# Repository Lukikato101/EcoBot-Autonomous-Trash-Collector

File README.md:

# EcoBot Autonomous Trash Collector

EcoBot is a prototype for an autonomous trash collection robot designed to streamline waste pickup in public spaces and improve environmental cleanliness. This project showcases a multidisciplinary approach combining mechanical design, embedded systems, and intelligent sensing.

## Project Summary

EcoBot integrates:
- autonomous navigation logic for route planning and obstacle avoidance
- AI-based object detection for identifying trash items
- embedded control for motors, sensors, and actuators
- mechanical design for effective trash intake and chassis stability

The repository includes CAD models, electronics design artifacts, and supporting documentation for the robot platform.

## Key Features

- Autonomous path planning and movement control
- Trash detection using computer vision methods
- Hardware-ready embedded system design
- Modular mechanical structure for rapid prototyping
- Focus on real-world usability and environmental impact

## Technical Stack
- Mechanical design: FreeCAD
- Embedded systems: Arduino-compatible microcontroller concepts
- AI / vision: YOLO-style object detection concepts
- Robotics middleware: ROS2 planned for future scalability
- Documentation & design review: KiCad, CAD files, and project notes

## Repository Structure

- `Embeddeds/` – electronics and firmware-related files
- `Mechanicals/` – CAD mechanical design files for the robot chassis
- `assets/references/` – supporting diagrams, reference materials, and design inspiration

## Why This Project Matters

EcoBot demonstrates the ability to deliver cross-functional engineering projects that blend hardware and software. It highlights practical skills in robotics design, embedded development, and intelligent sensing systems — all highly valuable for engineering and automation roles.

## Career Relevance

This project is ideal to mention in job applications because it reflects:
- hands-on prototyping experience
- multidisciplinary collaboration potential
- a clear focus on solving a social and environmental problem
- readiness to work with modern robotics and AI technologies

## Next Steps

Future enhancements planned for EcoBot include:
- full ROS2 integration for advanced autonomous behavior
- improved object detection accuracy with training datasets
- a remote monitoring dashboard for status visualization
- real-world field testing and performance validation

---

If you want, I can also help create a concise project summary for your resume or LinkedIn profile.

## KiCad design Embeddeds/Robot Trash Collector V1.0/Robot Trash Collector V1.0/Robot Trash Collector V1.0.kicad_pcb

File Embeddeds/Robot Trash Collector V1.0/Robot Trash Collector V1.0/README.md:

# Robot Trash Collector V1.0

## Project Overview
This project is a PCB-based embedded control system for a small autonomous robot designed for waste collection. The board integrates the main controller, motor-driving circuitry, power regulation, and sensing support in a compact and modular design.

The purpose of this system is to provide a reliable electronic platform for autonomous movement, basic sensing, and control of the robot's actuators. It is intended for educational use, prototyping, and further engineering development.

## Project Purpose
The purpose of this project is to provide a reliable electronic platform for controlling a mobile robot. The design aims to support:
- Precise motor control for movement
- Wireless communication capabilities through the main controller
- Sensor-based operation for improved automation
- A compact PCB layout suitable for prototyping and further development

## Main Hardware Components
The current design includes the following key components:
- ESP32-C3-WROOM-02: Main microcontroller module with Wi-Fi and Bluetooth LE support
- TB6612FNG: Dual H-bridge motor driver used to control DC motors efficiently
- AP2112K-3.3: 3.3V low-dropout voltage regulator for stable logic power
- MPU-6050: Motion and orientation sensor for attitude and motion feedback
- Push buttons: Reset and user interaction input
- Power and motor connectors: External supply and actuator connection points

## Functional Description
The board is organized around a simple control architecture:
1. Power is supplied through the main input connector.
2. The regulator converts the supply voltage into a stable 3.3V rail for the controller and sensing circuitry.
3. The ESP32-C3 module acts as the central controller for processing signals and managing communication.
4. The TB6612FNG motor driver receives control signals and drives the robot's motors.
5. The MPU-6050 provides motion-related feedback that can be used for navigation or stabilization logic.

This structure makes the design easy to understand, modify, and expand for future improvements.

## Project Structure
The workspace contains the following important files:
- Robot Trash Collector V1.0.kicad_sch: Schematic design
- Robot Trash Collector V1.0.kicad_pcb: PCB layout
- Robot Trash Collector V1.0.kicad_pro: KiCad project configuration
- Robot Trash Collector V1.0.step: 3D model export of the PCB
- Projects Image/: Reference images and project visuals
- docs/Block_Diagram.svg: System-level block diagram
- docs/production-checklist.md: Production readiness checklist
- docs/BOM.csv: Starter bill of materials

## How to Use This Project
1. Install KiCad on your computer.
2. Open the project file named Robot Trash Collector V1.0.kicad_pro.
3. Review the schematic and PCB layout carefully.
4. Run design rule checks (DRC) and electrical rule checks (ERC) before fabrication.
5. Verify component footprints and connector pin assignments before manufacturing.

## Production Readiness Notes
This design is close to a prototype-ready state, but it should still be reviewed carefully before mass production or a final manufacturing run. The most important items to confirm are:
- Proper component footprints and pin mapping
- Correct power polarity and regulator selection
- Adequate decoupling and grounding
- Clear silkscreen labeling for connectors and test points
- A verified prototype build and functional test

## Visual Documentation
The following visual assets are available to help understand the project more clearly:

- Schematic and PCB layout: Open the KiCad project files in the project folder
- Block diagram: [docs/Block_Diagram.svg](docs/Block_Diagram.svg)
- Project image preview: [Projects Image/Robot Trash Collector V1.0.svg](Projects%20Image/Robot%20Trash%20Collector%20V1.0.svg)
- Additional screenshots: [Projects Image](Projects%20Image)

These visuals provide a quick overview of the overall architecture, component placement, and system layout.

## Development Notes
This design is intended for educational, prototyping, and engineering development purposes. It can be further improved by adding:
- A complete bill of materials (BOM)
- Firmware documentation
- Testing procedures and calibration instructions
- A finalized assembly drawing
- A more detailed schematic annotation for easier manufacturing review

## Notes for Production Readiness
Before sending the board to fabrication, it is strongly recommended to:
- Review the schematic and PCB layout carefully in KiCad
- Verify all footprints and pin assignments
- Confirm power polarity and regulator compatibility
- Check grounding, decoupling, and connector labeling
- Build and test a prototype before final production

## Summary
Robot Trash Collector V1.0 is a compact embedded electronics project that combines microcontroller control, motor driving, sensor integration, and power management in a single PCB design. It provides a solid foundation for building and expanding an autonomous robotic system.

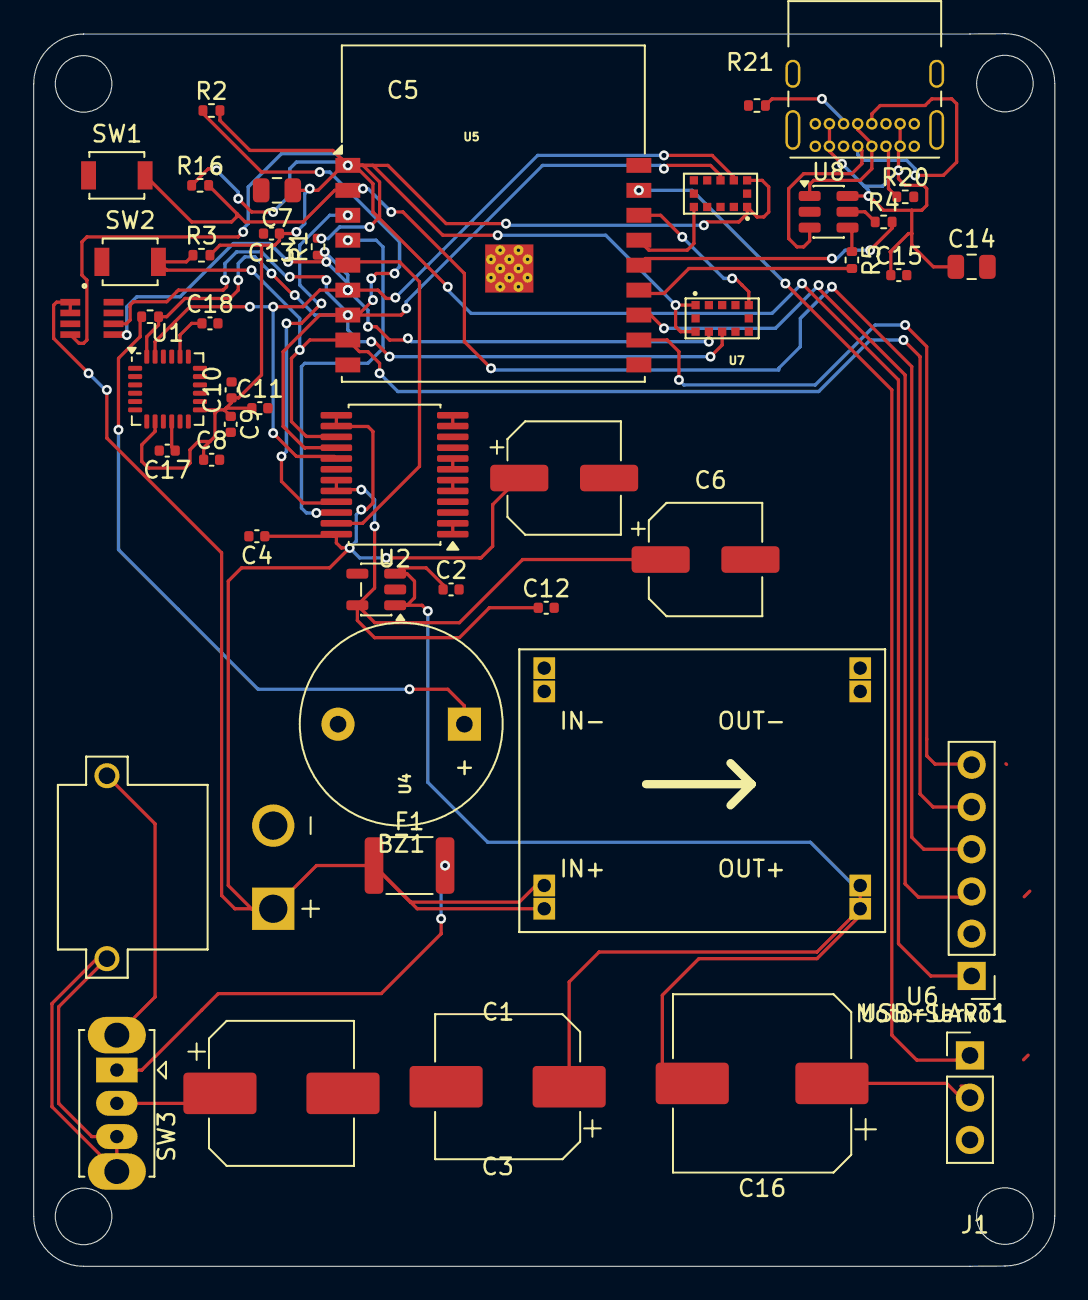
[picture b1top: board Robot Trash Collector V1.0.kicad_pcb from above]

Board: 2 copper layers, 61.4 x 74.1 mm, 45 parts (0 on the bottom side), 35 nets.

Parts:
BZ1: Buzzer; Buzzer_12x9.5RM7.6
C1, C3: 220uF; CP_Elec_8x10.5
C2, C4, C8, C9, C10, C11, C12, C13, C15, C17: 100nF; C_0402_1005Metric
C5, C6: 100uF; CP_Elec_6.3x7.7
C7, C14: 10uF; C_0805_2012Metric
C16: 470uF; CP_Elec_10x10.5
C18: 2.2nF; C_0402_1005Metric
F1: Polyfuse_Small; Fuse_1812_4532Metric
J1: USB_C_Receptacle_USB2.0_16P; USB_C_Receptacle_GCT_USB4085
J2: XT30PW-M; AMASS_XT30PW-M
MotorServo1: Conn_01x03; PinHeader_1x03_P2.54mm_Vertical
R1, R2: 4.7K; R_0402_1005Metric
R3, R16: 10K; R_0402_1005Metric
R4, R5: 22; R_0402_1005Metric
R19: 220; R_0402_1005Metric
R20, R21: 5.1K; R_0402_1005Metric
SW1: SW_Push_Button_Reset; SW_SPST_B3U-1000P
SW2: SW_Push_Button_Boot; SW_SPST_B3U-1000P
SW3: SW_SPST; SW_Slide_SPDT_Straight_CK_OS102011MS2Q
U1: MPU-6050; InvenSense_QFN-24_4x4mm_P0.5mm
U2: TB6612FNG; SSOP-24_5.3x8.2mm_P0.65mm
U3: MP1584 Module; DC-BRICK
U4: INA219; SOT23-8
U5, U7: VL53L0X; SENSOR_VL53L0X
U6: ESP32-C3-WROOM-02
U8: USBLC6-2SC6; SOT-23-6
U9: AP2112K-3.3; SOT-23-5
USB-UART1: Conn_01x06; PinHeader_1x06_P2.54mm_Vertical

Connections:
3V3: C7.1, C8.1, C9.1, C10.1, C11.1, C13.1, R1.2, R2.2, R3.2, R16.1, U1.8 (VLOGIC), U1.13 (VDD), U4.4 (VCC), U5.1 (AVDDVCSEL), U5.11 (AVDD), U6.1 (3V3), U7.1 (AVDDVCSEL), U7.11 (AVDD), USB-UART1.1
+3.3V AP: C6.1, C12.1, U2.19 (STBY), U2.20 (VCC), U9.5 (VOUT)
+5V MP: C2.1, C3.1, C16.2, U3.OUT1+ (VOUT+), U3.OUT2+ (VOUT+), U9.1 (VIN), U9.3 (EN)
+5V_USB: C14.1, C15.1, J1.A4 (VBUS), J1.A9 (VBUS), J1.B4 (VBUS), J1.B9 (VBUS), U8.6 (I/O1)
BAT 7.4V: C1.1, C4.1, C5.1, F1.1, J2.P, SW3.2 (B), U2.13 (VM2), U2.14 (VM3), U2.24 (VM1), U3.IN1+ (VIN+), U3.IN2+ (VIN+), U4.1 (VIN+), U4.2 (VIN-)
BOOT: R3.1, SW2.2, U2.15 (PWMB), U6.8 (IO9), USB-UART1.5
GND: BZ1.2 (-), C1.2, C2.2, C3.2, C4.2, C5.2, C6.2, C7.2, C8.2, C9.2, C10.2, C11.2, C12.2, C13.2, C14.2, C15.2, C17.2, C18.2, J1.A1 (GND), J1.A12 (GND), J1.B1 (GND), J1.B12 (GND), J1.S1 (SHIELD), J2.N, MotorServo1.3, R20.2, R21.2, SW1.1, SW2.1, U1.9 (AD0), U1.18 (GND), U2.3 (PGND1), U2.4 (PGND1), U2.9 (PGND2), U2.10 (PGND2), U2.18 (GND), U3.IN1- (VIN-), U3.IN2- (VIN-), U3.OUT1- (VOUT-), U3.OUT2- (VOUT-), U4.3 (GND), U4.7 (A0), U4.8 (A1), U5.2 (AVSSVCSEL), U5.3 (GND), U5.4 (GND), U5.6 (GND), U5.12 (GND), U6.9 (GND), U6.19 (GND), U7.2 (AVSSVCSEL), U7.3 (GND), U7.4 (GND), U7.6 (GND), U7.12 (GND), U8.2 (GND), U9.2 (GND), USB-UART1.2
GPIO04: U2.21 (AIN1), U6.3 (IO4)
GPIO05: U2.22 (AIN2), U6.4 (IO5)
GPIO06: U2.23 (PWMA), U6.5 (IO6)
GPIO07: R1.1, U1.23 (SCL), U2.17 (BIN1), U4.5 (SCL), U5.10 (SCL), U6.6 (IO7), U7.10 (SCL)
GPIO08: R2.1, R19.1, U1.24 (SDA), U2.16 (BIN2), U4.6 (SDA), U5.9 (SDA), U6.7 (IO8), U7.9 (SDA)
GPIO18: R5.2, U6.13 (IO18)
GPIO19: R4.2, U6.14 (IO19)
I02: U5.5 (~XSHUT), U6.16 (IO2)
I2C_SCL: U6.12 (IO21/TXD), USB-UART1.3
I2C_SDA: U6.11 (IO20/RXD), USB-UART1.6
IO1: MotorServo1.1, U6.17 (IO1)
IO3: U6.15 (IO3), U7.5 (~XSHUT)
Motor A+: U2.1 (AO1), U2.2 (AO1)
Motor A-: U2.5 (AO2), U2.6 (AO2)
Motor B+: U2.11 (BO1), U2.12 (BO1)
Motor B-: U2.7 (BO2), U2.8 (BO2)
unnamed: BZ1.1 (+), R19.2
unnamed: J1.A5 (CC1), R20.1
unnamed: J1.B5 (CC2), R21.1
unnamed: C16.1, MotorServo1.2
unnamed: F1.2, SW3.1 (A)
unnamed: C18.1, U1.20 (CPOUT)
unnamed: C17.1, U1.10 (REGOUT)
RST: R16.2, SW1.2, U6.2 (EN), USB-UART1.4
USBLC6 Pin 1: J1.A6 (D+), J1.B6 (D+), U8.1 (I/O1)
USBLC6 Pin 3: J1.A7 (D-), J1.B7 (D-), U8.3 (I/O2)
USBLC6 Pin 4: R5.1, U8.4 (I/O2)
USBLC6 Pin 5: R4.1, U8.5 (VBUS)

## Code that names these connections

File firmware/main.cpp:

#include <Arduino.h>
#include <Wire.h>

// ESP32-C3 pin mapping from PCB footprint
static const int PIN_GPIO04 = 4;
static const int PIN_GPIO05 = 5;
static const int PIN_GPIO06 = 6;
static const int PIN_GPIO07 = 7;
static const int PIN_GPIO08 = 8;
static const int PIN_GPIO09 = 9;
static const int PIN_GPIO10 = 10;
static const int PIN_GPIO18 = 18;
static const int PIN_GPIO19 = 19;
static const int PIN_IO3 = 3;
static const int PIN_IO2 = 2;
static const int PIN_IO1 = 1;
static const int PIN_IO0 = 0;

// I2C pins used by INA219, MPU-6050, VL53L0X
// On the ESP32-C3 WROOM-02 footprint these are labeled IO20/RXD and IO21/TXD
static const int PIN_I2C_SDA = 20;
static const int PIN_I2C_SCL = 21;

// TB6612FNG control pins on ESP32
static const int MOTOR_A_PWM = PIN_GPIO06;   // PWMA
static const int MOTOR_A_IN1 = PIN_GPIO04;   // AIN1
static const int MOTOR_A_IN2 = PIN_GPIO05;   // AIN2
static const int MOTOR_B_PWM = PIN_GPIO09;   // PWMB
static const int MOTOR_B_IN1 = PIN_GPIO07;   // BIN1
static const int MOTOR_B_IN2 = PIN_GPIO08;   // BIN2

// Note: TB6612FNG STBY is tied to +3.3V on this board, so it is always enabled.

void setup() {
  Serial.begin(115200);
  delay(100);

  pinMode(MOTOR_A_PWM, OUTPUT);
  pinMode(MOTOR_A_IN1, OUTPUT);
  pinMode(MOTOR_A_IN2, OUTPUT);
  pinMode(MOTOR_B_PWM, OUTPUT);
  pinMode(MOTOR_B_IN1, OUTPUT);
  pinMode(MOTOR_B_IN2, OUTPUT);

  pinMode(PIN_I2C_SDA, INPUT_PULLUP);
  pinMode(PIN_I2C_SCL, INPUT_PULLUP);

  digitalWrite(MOTOR_A_PWM, LOW);
  digitalWrite(MOTOR_A_IN1, LOW);
  digitalWrite(MOTOR_A_IN2, LOW);
  digitalWrite(MOTOR_B_PWM, LOW);
  digitalWrite(MOTOR_B_IN1, LOW);
  digitalWrite(MOTOR_B_IN2, LOW);

  Wire.begin(PIN_I2C_SDA, PIN_I2C_SCL);

  Serial.println("EcoBot firmware starting...");
}

void loop() {
  // Simple motor test sequence
  // Motor standby is permanently enabled on this board.

  // Drive motor A forward
  digitalWrite(MOTOR_A_IN1, HIGH);
  digitalWrite(MOTOR_A_IN2, LOW);
  analogWrite(MOTOR_A_PWM, 128);

  // Drive motor B forward
  digitalWrite(MOTOR_B_IN1, HIGH);
  digitalWrite(MOTOR_B_IN2, LOW);
  analogWrite(MOTOR_B_PWM, 128);

  delay(1000);

  // Stop motors
  analogWrite(MOTOR_A_PWM, 0);
  analogWrite(MOTOR_B_PWM, 0);

  delay(1000);
}
